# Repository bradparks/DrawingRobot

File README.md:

# DrawingRobot
Progetto per lo sviluppo di piccoli robot controllabili via bluetooth in grado di muoversi e disegnare sul piano in cui si muovono

Overview:
http://dev.hacklabterni.org/projects/drawrobot2015/

Wiki:
http://dev.hacklabterni.org/projects/drawrobot2015/wiki

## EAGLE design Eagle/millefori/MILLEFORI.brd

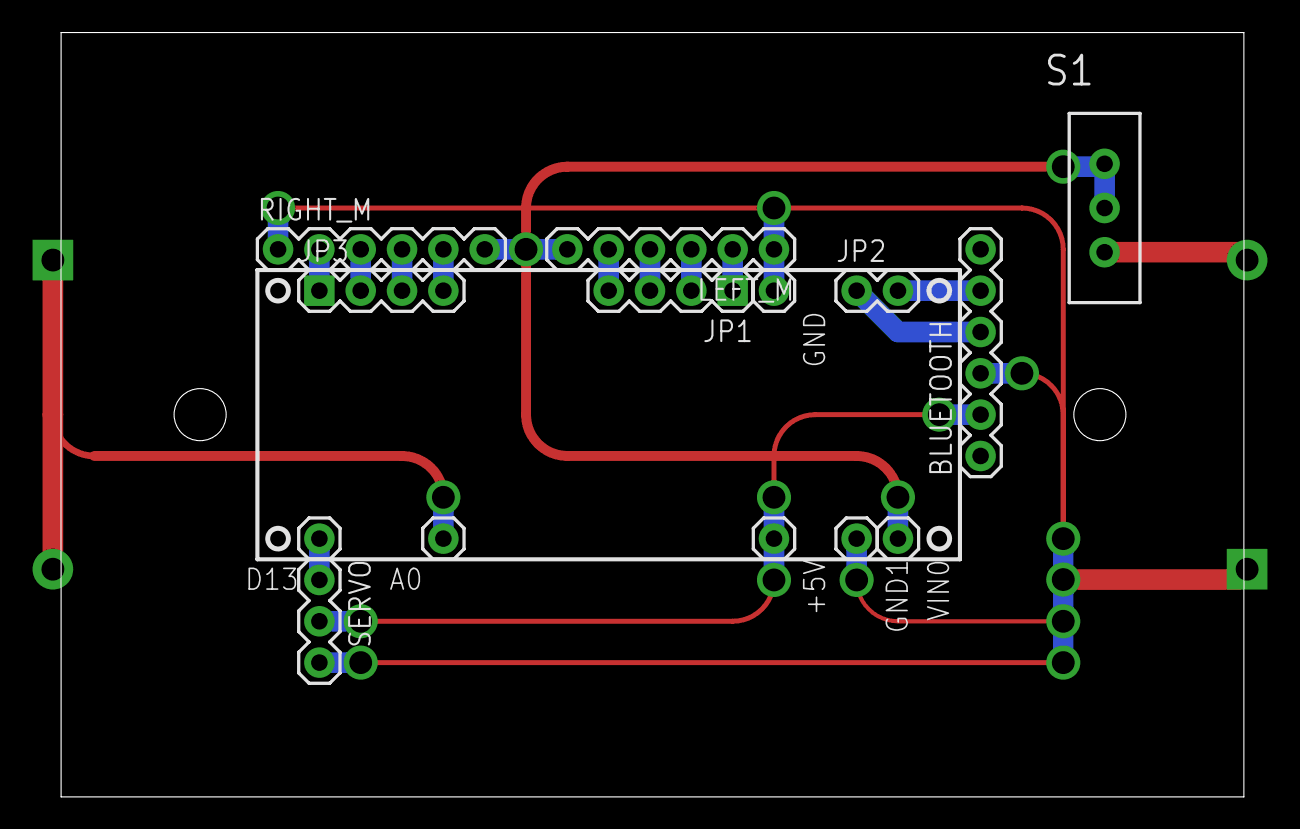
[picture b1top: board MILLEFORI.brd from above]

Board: 2 copper layers, 72.7 x 47.0 mm, 15 parts (0 on the bottom side), 16 nets.

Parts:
+5V: 1X01
A0: 1X01
BLUETOOTH: 1X06
D13: 1X01
GND, GND1: 1X01
JP1, JP3: 1X04
JP2: 1X02
LEFT_M: 1X06
RIGHT_M: 1X06
S1: SWITCH-SPDT_LOCK.007S
SERVO: 1X03
U$3: 18650; BATTERY_PACK_18650
VIN0: 1X01

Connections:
+5V: +5V.1, BLUETOOTH.2, SERVO.2
+7,2V: S1.3, U$3.+3.7V_1
A0: A0.1, U$3.+3.7V_2, U$3.GND_1
D0/RX: BLUETOOTH.5, JP2.2
D1/TX: BLUETOOTH.4, JP2.1
D2: JP1.1, LEFT_M.2
D3: JP1.2, LEFT_M.3
D4: JP1.3, LEFT_M.4
D5: JP1.4, LEFT_M.5
D9: JP3.1, RIGHT_M.2
D10: JP3.2, RIGHT_M.3
D11: JP3.3, RIGHT_M.4
D12: JP3.4, RIGHT_M.5
D13: D13.1, SERVO.1
GND: BLUETOOTH.3, GND.1, GND1.1, LEFT_M.1, RIGHT_M.1, SERVO.3, U$3.GND_2
VIN: LEFT_M.6, RIGHT_M.6, S1.1, S1.2, VIN0.1

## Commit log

2016-01-24 change md to rst
2016-01-24 add logo
2016-02-04 First release
2016-02-04 change steps_rev
2016-02-04 change pin order, add Callback function
2016-02-04 fine adjustment
2016-02-04 inverted CW and CCW
2016-02-04 add acceleration and deceleration
2016-02-04 ConfigurableFirmata
2016-02-04 OpenSCAD
2016-02-04 Fritzing
2016-03-03 Pezzi usati
    raccolta di .stl .scad. immagini e datasheet dei componenti utilizzati
2016-03-03 Chassis +supporto motori
2016-03-05 quello che va sulla protoBoard
2016-03-06 clear old methods
2016-03-07 pezzi finiti lavori in corso
2016-03-08 manca nuovo supporto servo
    union stampabile da testare
2016-03-08 insieme
2016-03-08 cuore
2016-03-10 rev0.1
2016-03-14 demo render ottagono più triangolo
2016-03-14 bozza
2016-03-16 da stampare?
2016-03-16 gcode
2016-03-16 RENDER
2016-03-16 smussa
2016-03-20 barre uguali
2016-03-21 Fork ConfigurableFirmate
2016-03-21 Change README
2016-03-21 change html
2016-03-23 DrawingRobot 2x18650 New Battery
2016-03-24 Aggiunto il blocco done al termine del disegno
2016-03-24 DrawingRobot in Snap4Arduino
2016-03-25 2 pezzi + slicer hephestos2 config
2016-03-25 SCHEMA ELETTRICO
2016-03-28 errata corrige tx-rx
2016-03-28 eagle2
2016-03-30 ruote e collatino penna
2016-04-02 Ruota 8 Raggi + Collare Penna
2016-05-27 png allineata con brd

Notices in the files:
parts and their libraries:
SparkFun-Connectors: Licensing: Creative Commons ShareAlike 4.0 International - https://creativecommons.org/licenses/by-sa/4.0
